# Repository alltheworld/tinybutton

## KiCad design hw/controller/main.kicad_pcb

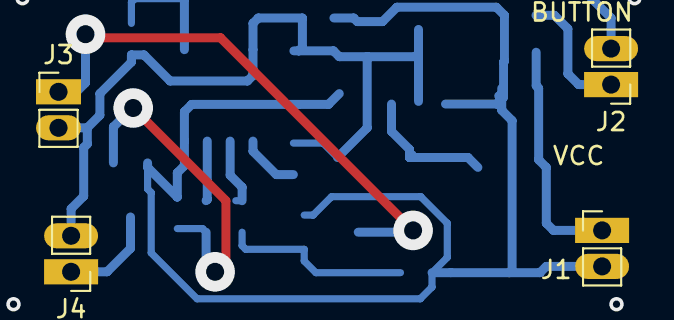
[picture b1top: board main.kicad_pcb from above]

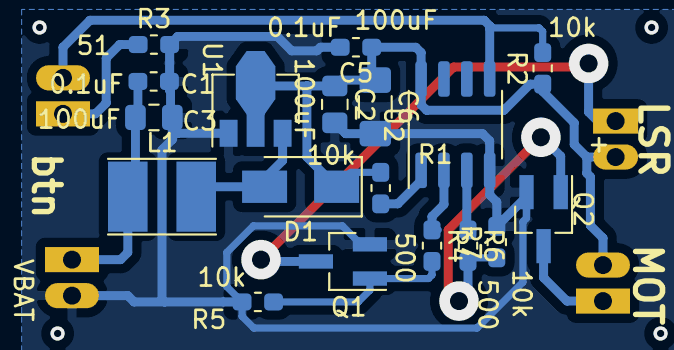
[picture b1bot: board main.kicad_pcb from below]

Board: 2 copper layers, 22 parts (18 on the bottom side), 13 nets.

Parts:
C1, C5: 0.1uF; C_0603_1608Metric_Pad1.05x0.95mm_HandSolder
C2, C3: 100uF; C_0805_2012Metric_Pad1.15x1.40mm_HandSolder
C6: 100uF; C_1206_3216Metric_Pad1.42x1.75mm_HandSolder
D1: SS14; D_SMA
J1: VBAT; PinHeader_1x02_P2.00mm_Vertical
J2: BUTTON; PinHeader_1x02_P2.00mm_Vertical
J3: PWR_LASER; PinHeader_1x02_P2.00mm_Vertical
J4: PWR_MOTOR; PinHeader_1x02_P2.00mm_Vertical
L1: 47uH; L_Taiyo-Yuden_NR-40xx_HandSoldering
Q1, Q2: Q_NPN_BEC; SOT-23_Handsoldering
R1, R2, R5, R7: 10k; R_0603_1608Metric_Pad1.05x0.95mm_HandSolder
R3: 51; R_0603_1608Metric_Pad1.05x0.95mm_HandSolder
R4, R6: 500; R_0603_1608Metric_Pad1.05x0.95mm_HandSolder
U1: CE8301; SOT-89-3
U2: ATtiny13A-SU; SOP-8_3.76x4.96mm_P1.27mm

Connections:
/PWR_LASER: J3.1, Q1.3
/PWR_MOT: J4.1, Q2.3
/RESET: R1.2, U2.1
/STEP_UP_CE8301/VCC: C1.1, C3.1, J1.1, L1.1
BUTTON: J2.2, R2.2, U2.5
Earth: C1.2, C2.2, C3.2, C5.2, C6.2, J1.2, Q1.2, Q2.2, R3.2, R5.2, R7.2, U1.1, U2.4
LASER: R4.1, U2.2
MOTOR: R6.1, U2.3
unnamed: D1.2, L1.2, U1.3
unnamed: J2.1, R3.1
unnamed: Q1.1, R4.2, R5.1
unnamed: Q2.1, R6.2, R7.1
VCC5V: C2.1, C5.1, C6.1, D1.1, J3.2, J4.2, R1.1, R2.1, U1.2, U2.8

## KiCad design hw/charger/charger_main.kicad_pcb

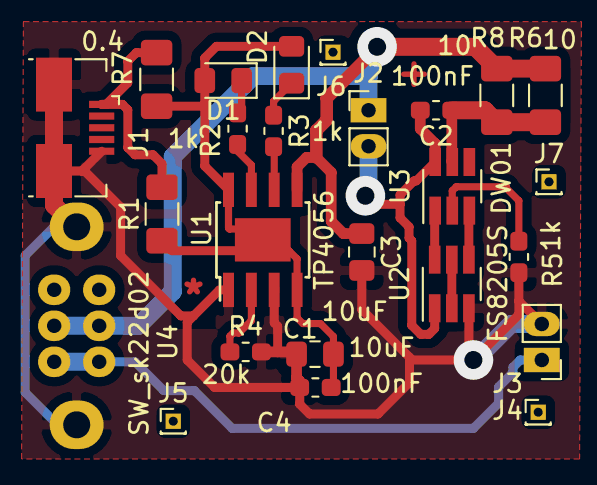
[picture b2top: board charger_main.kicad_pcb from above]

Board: 2 copper layers, 25 parts (0 on the bottom side), 16 nets.

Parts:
C1, C3: 10uF; C_0805_2012Metric_Pad1.15x1.40mm_HandSolder
C2, C4: 100nF; C_0603_1608Metric_Pad1.05x0.95mm_HandSolder
D1, D2: LED; LED_0805_2012Metric_Pad1.15x1.40mm_HandSolder
J1: USB_B_Micro; USB_Micro-footprint1
J2: BattConnector; PinHeader_1x02_P2.00mm_Vertical
J3: PwrConnector; PinHeader_1x02_P2.00mm_Vertical
J4, J5, J6, J7: Position; PinHeader_1x01_P1.00mm_Vertical
R1, R7: 0.4; R_1206_3216Metric_Pad1.42x1.75mm_HandSolder
R2, R3, R5: 1k; R_0603_1608Metric_Pad1.05x0.95mm_HandSolder
R4: 20k; R_0603_1608Metric_Pad1.05x0.95mm_HandSolder
R6, R8: 10; R_1206_3216Metric_Pad1.42x1.75mm_HandSolder
U1: TP4056; TI_SO-PowerPAD-8
U2: FS8205S; SOT-23-6_Handsoldering
U3: DW01; SOT-23-6_Handsoldering
U4: SW_sk22d02; SW_SK22D02_DPDT_Angled

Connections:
/tp4056module/BatGND: C2.2, J2.2, U2.1, U3.6
/tp4056module/CHRG: R2.2, U1.7
/tp4056module/CS: R5.2, U3.2
/tp4056module/DW01VCC: C2.1, R6.2, R8.2, U3.5
/tp4056module/G1: U2.6, U3.1
/tp4056module/G2: U2.4, U3.3
/tp4056module/LED_CHRG: D1.1, R2.1
/tp4056module/LED_STDBY: D2.1, R3.1
/tp4056module/PROG: R4.1, U1.2
/tp4056module/STDBY: R3.2, U1.6
/tp4056module/Vcc: C1.1, C4.1, D1.2, D2.2, R1.1, R7.1, U1.4, U1.8, U1.9
GND: C1.2, C3.2, C4.2, J1.5, J1.6, J3.2, R4.2, R5.1, U1.1, U1.3, U2.3, U4.7, U4.8
unnamed: U2.2, U2.5
PwrON: J3.1, U4.3, U4.6
USBVCC: J1.1, R1.2, R7.2
Vcc3V: C3.1, J2.1, R6.1, R8.1, U1.5, U4.2, U4.5

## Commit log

2016-12-06 Add files
2017-02-26 total update
2017-02-26 remove old c++
2018-07-04 cleaning. update.
2019-08-08 version 0.2
2019-08-10 add readme
